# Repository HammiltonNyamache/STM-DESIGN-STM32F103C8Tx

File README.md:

# STM-DESIGN-STM32F103C8Tx
Custom STM32F103C8T6 development board designed in KiCad. The design includes USB power input, AMS1117 3.3V regulation, SWD programming interface, UART and I2C headers, external 16 MHz crystal oscillator, and proper decoupling and filtering for stable MCU operation.

## Overview
This repository contains the KiCad design files for a custom STM32F103C8T6 development board. The board integrates power regulation, USB connectivity, programming/debugging interfaces, and communication headers for embedded development.

The project was designed using KiCad 9 and demonstrates the complete workflow of schematic design, PCB layout, and manufacturing file generation.

## Features
- STM32F103C8T6 ARM Cortex-M3 microcontroller
- USB Micro-B interface
- 3.3V voltage regulation using AMS1117
- 16 MHz external crystal oscillator
- SWD programming and debugging interface
- UART communication header
- I2C communication interface
- Power indication LED
- Proper decoupling and analog filtering
- Mounting holes for mechanical support

## Hardware Architecture

### Power Supply
The board is powered through a USB Micro-B connector. The input voltage (VBUS) is regulated to 3.3V using an AMS1117-3.3 linear voltage regulator.  
Filtering capacitors are used to stabilize the supply voltage and reduce noise.

### Microcontroller
The main controller used is the STM32F103C8T6, a 32-bit ARM Cortex-M3 microcontroller.  
It operates at 3.3V and supports multiple communication peripherals including UART, I2C, SPI, and USB.

### Clock System
An external 16 MHz crystal oscillator is connected to the MCU to provide a stable clock source.  
Two load capacitors are used to stabilize the oscillator.

### USB Interface
The microcontroller is connected to a USB Micro-B connector through the D+ and D- lines.  
A pull-up resistor is used to enable USB device detection.

### Debugging Interface
An SWD (Serial Wire Debug) interface is provided for programming and debugging using tools such as:

- ST-Link
- OpenOCD
- STM32CubeProgrammer

### Communication Interfaces
The board exposes communication headers for external peripherals:

**UART**
- TX
- RX
- GND
- 3.3V

**I2C**
- SDA
- SCL
- GND
- 3.3V

### Analog Power Filtering
A ferrite bead and filtering capacitors are used to isolate the analog supply (VDDA) from digital noise.

### Decoupling
Multiple decoupling capacitors are placed near the MCU power pins to ensure stable operation.

## Tools Used
- KiCad 9.0
- STM32F103C8T6 Microcontroller
- AMS1117-3.3 Voltage Regulator

## Applications
This board can be used for:

- Embedded systems development
- STM32 firmware experimentation
- Learning ARM Cortex-M microcontrollers
- Rapid prototyping
- Educational embedded electronics projects

## Author
Designed as part of an embedded hardware design project by HAMMILTON NYAMACHE  using KiCad.

## PCB Design
### Shcematic

### Top Layer

### Bottom Layer

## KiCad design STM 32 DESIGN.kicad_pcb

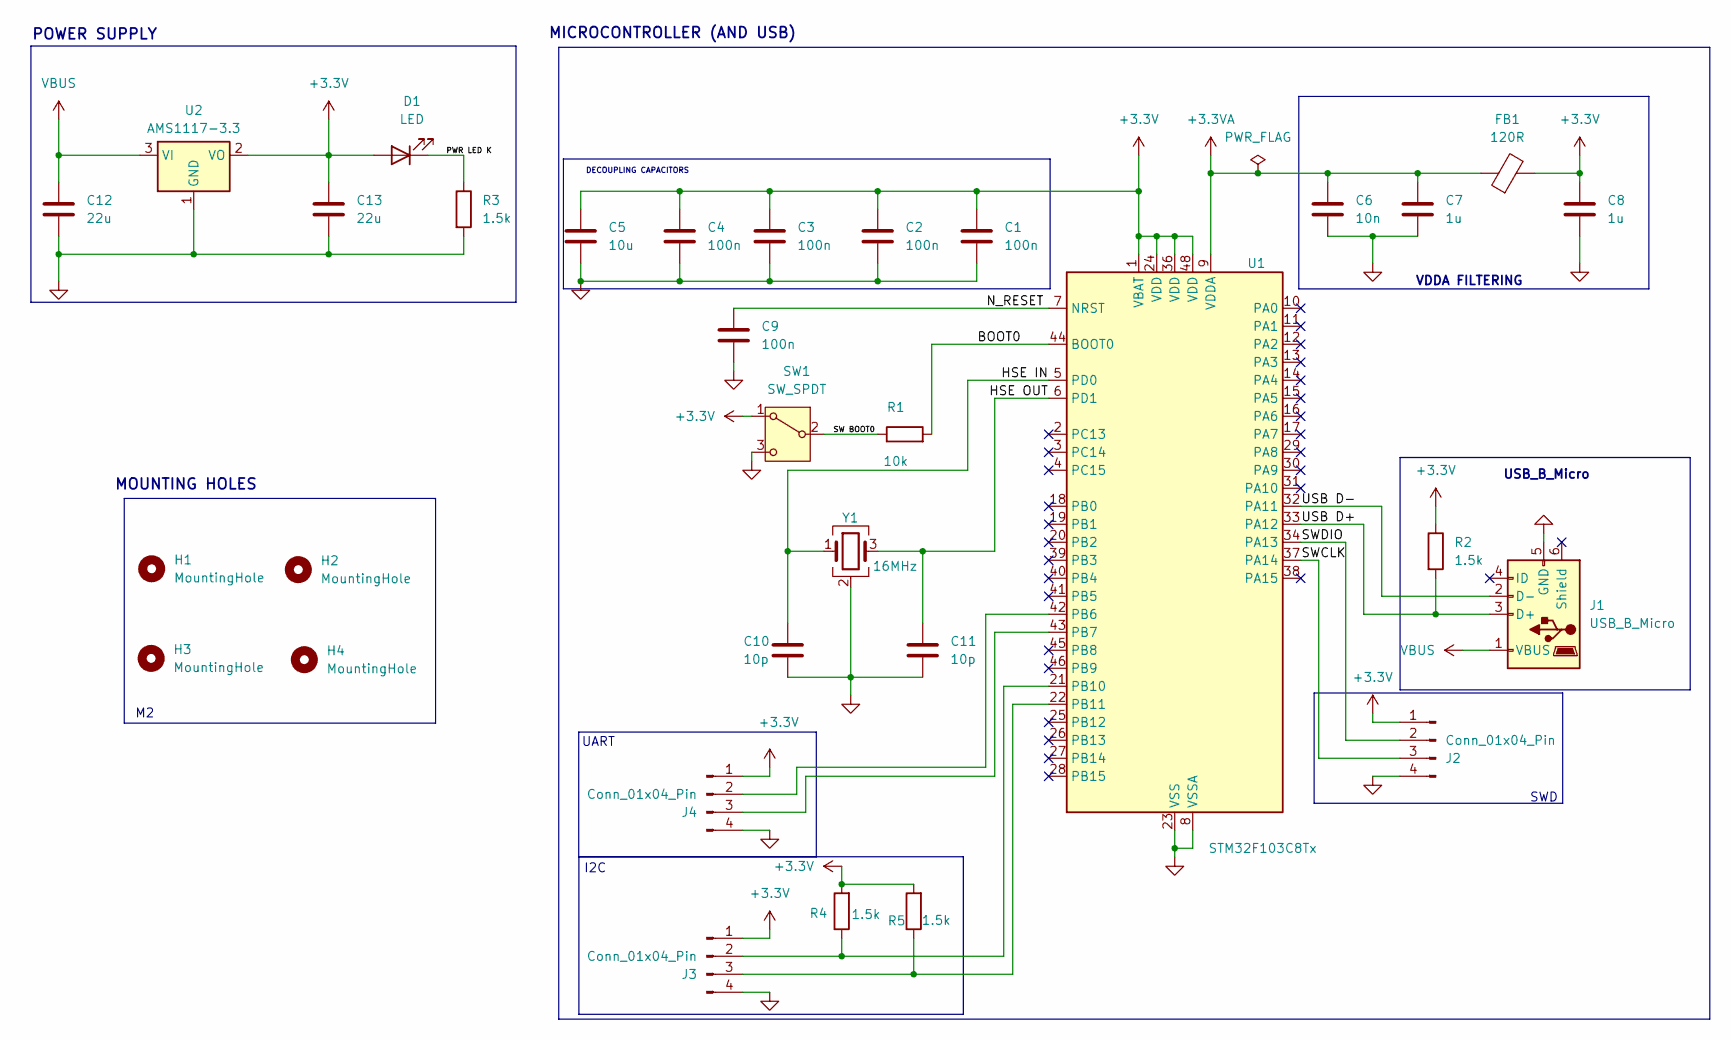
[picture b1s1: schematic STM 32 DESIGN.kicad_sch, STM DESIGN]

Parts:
C1, C2, C3, C4, C9: 100n; C_0402_1005Metric
C5: 10u; C_0603_1608Metric
C6: 10n; C_0402_1005Metric
C7, C8: 1u; C_0402_1005Metric
C10, C11: 10p; C_0402_1005Metric
C12, C13: 22u; C_0805_2012Metric
D1: LED; LED_0603_1608Metric
FB1: 120R; L_0603_1608Metric
H1, H2, H3, H4: MountingHole; MountingHole_2.2mm_M2
J1: USB_B_Micro; USB_Micro-B_Wuerth_629105150521
J2, J3, J4: Conn_01x04_Pin; PinHeader_1x04_P2.54mm_Vertical
R1: 10k; R_0402_1005Metric
R2, R3, R4, R5: 1.5k; R_0402_1005Metric
SW1: SW_SPDT; SW_SPDT_PCM12
U1: STM32F103C8Tx; LQFP-48_7x7mm_P0.5mm
U2: AMS1117-3.3; SOT-223-3_TabPin2
Y1: 16MHz; Crystal_SMD_3225-4Pin_3.2x2.5mm

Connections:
+3.3V: C1.1, C2.1, C3.1, C4.1, C5.1, C8.1, C13.1, D1.2 (A), FB1.2, J2.1, J3.1, J4.1, R2.1, R4.2, R5.2, SW1.1 (A), U1.1 (VBAT), U1.24 (VDD), U1.36 (VDD), U1.48 (VDD), U2.2 (VO)
+3.3VA: C6.1, C7.1, FB1.1, U1.9 (VDDA)
/BOOT0: R1.2, U1.44 (BOOT0)
/HSE IN: C10.1, U1.5 (PD0), Y1.1
/HSE OUT: C11.1, U1.6 (PD1), Y1.3
/N_RESET: C9.1, U1.7 (NRST)
/PWR LED K: D1.1 (K), R3.1
/SW BOOT0: R1.1, SW1.2 (B)
/SWCLK: J2.3, U1.37 (PA14)
/SWDIO: J2.2, U1.34 (PA13)
/USB D+: J1.3 (D+), R2.2, U1.33 (PA12)
/USB D-: J1.2 (D-), U1.32 (PA11)
GND: C1.2, C2.2, C3.2, C4.2, C5.2, C6.2, C7.2, C8.2, C9.2, C10.2, C11.2, C12.2, C13.2, J1.5 (GND), J2.4, J3.4, J4.4, R3.2, SW1.3 (C), U1.8 (VSSA), U1.23 (VSS), U1.35 (VSS), U1.47 (VSS), U2.1 (GND), Y1.2 (G), Y1.4 (G)
unnamed: J3.2, R4.1, U1.21 (PB10)
unnamed: J3.3, R5.1, U1.22 (PB11)
unnamed: J4.2, U1.42 (PB6)
unnamed: J4.3, U1.43 (PB7)
VBUS: C12.1, J1.1 (VBUS), U2.3 (VI)

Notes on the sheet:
POWER SUPPLY
SWD
UART
VDDA FILTERING
USB_B_Micro
DECOUPLING CAPACITORS
MOUNTING HOLES
MICROCONTROLLER (AND USB)
I2C

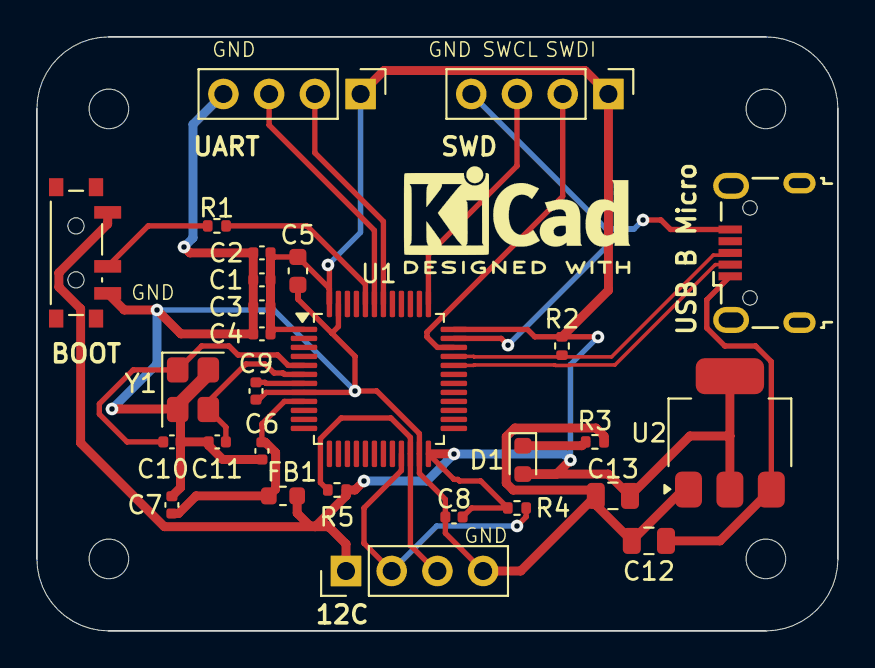
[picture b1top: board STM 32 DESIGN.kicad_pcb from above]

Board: 2 copper layers, 44.5 x 33.0 mm, 32 parts (0 on the bottom side), 18 nets.

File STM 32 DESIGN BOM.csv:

Comment,Designator,Footprint,JLCPCB Part
100n,"C1,C2,C3,C4,C9",Capacitor_SMD:C_0402_1005Metric,C1525
10u,C5,Capacitor_SMD:C_0603_1608Metric,C1691
10n,C6,Capacitor_SMD:C_0402_1005Metric,C1524
1u,"C7,C8",Capacitor_SMD:C_0402_1005Metric,C14445
10p,"C10,C11",Capacitor_SMD:C_0402_1005Metric,C32949
22u,"C12,C13",Capacitor_SMD:C_0805_2012Metric,C5674
LED,D1,LED_SMD:LED_0603_1608Metric,C2286
120R,FB1,Inductor_SMD:L_0603_1608Metric,C160983
16MHz,Y1,Crystal:Crystal_SMD_3225-4Pin_3.2x2.5mm,C518162
USB_B_Micro,J1,Connector_USB:USB_Micro-B_Wuerth_629105150521,C2894326
Conn_01x04_Pin,"J2,J3,J4",Connector_PinHeader_2.54mm:PinHeader_1x04_P2.54mm_Vertical,C2905435
10k,R1,Resistor_SMD:R_0402_1005Metric,C22356213
1.5k,"R2,R3,R4,R5",Resistor_SMD:R_0402_1005Metric,C22369162
SW_SPDT,SW1,Button_Switch_SMD:SW_SPDT_PCM12,C221841
STM32F103C8Tx,U1,Package_QFP:LQFP-48_7x7mm_P0.5mm,C8734
AMS1117-3.3,U2,Package_TO_SOT_SMD:SOT-223-3_TabPin2,C347222

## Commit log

2026-03-11 Enhance README with project details and architecture
    Expanded README with detailed project overview, features, hardware architecture, and communication interfaces.
2026-03-11 Update README with tools, applications, and design info
    Added sections for tools used, applications, author, and PCB design.
2026-03-11 Create IMAGES
2026-03-11 Revise project title in README.md
    Updated project title in README.md for clarity.
2026-03-12 Fix grammatical error in author section
2026-03-12 Add schematic section to README
2026-03-12 Update schematic image path in README
